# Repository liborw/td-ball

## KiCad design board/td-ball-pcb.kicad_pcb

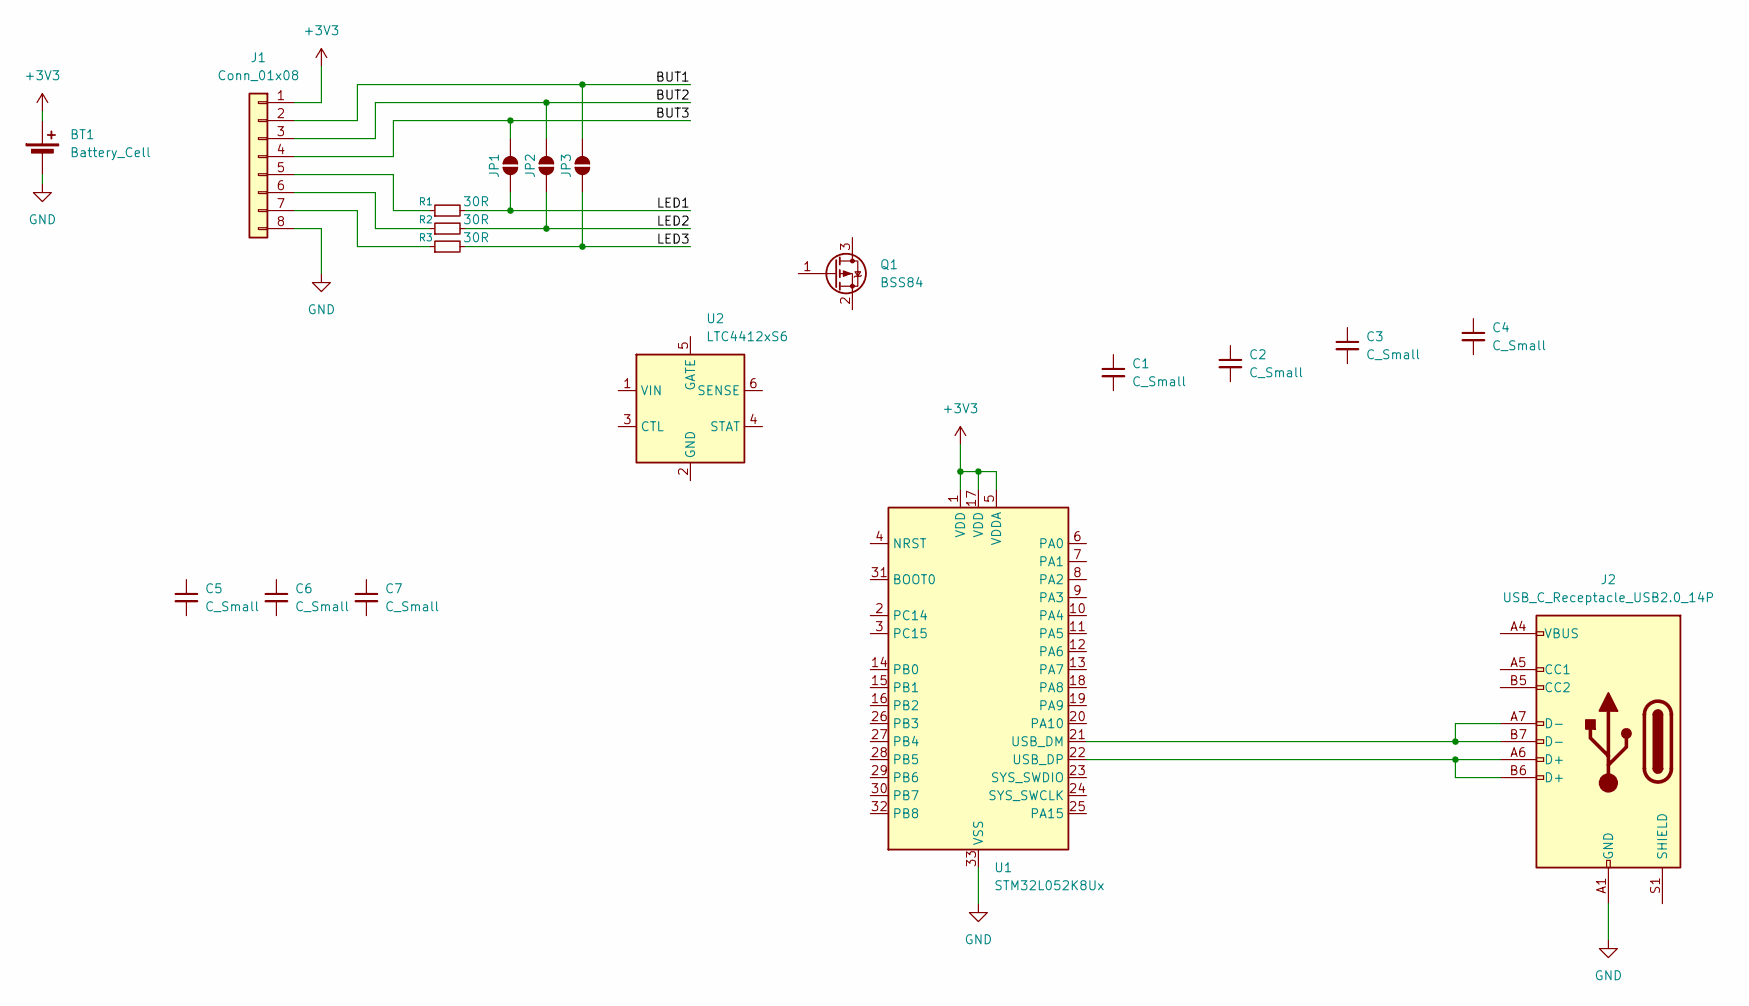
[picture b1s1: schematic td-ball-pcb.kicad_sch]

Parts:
BT1: Battery_Cell; MYOUNG_BS-24-B4AA016_CR2450
C1, C2, C3, C4: C_Small; C_0603_1608Metric
C5, C6, C7: C_Small; C_1210_3225Metric
J1: Conn_01x08; JST_SH_BM08B-SRSS-TB_1x08-1MP_P1.00mm_Vertical
J2: USB_C_Receptacle_USB2.0_14P; USB_C_Receptacle_G-Switch_GT-USB-7051x
JP1, JP2, JP3: SolderJumper_2_Open; SolderJumper-2_P1.3mm_Open_RoundedPad1.0x1.5mm
Q1: BSS84; SOT-23
R1, R2, R3: 30R; R_0603_1608Metric
U1: STM32L052K8Ux; QFN-32-1EP_5x5mm_P0.5mm_EP3.45x3.45mm
U2: LTC4412xS6; TSOT-23-6

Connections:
+3V3: BT1.1 (+), J1.1, U1.1 (VDD), U1.5 (VDDA), U1.17 (VDD)
/BUT1: J1.2, JP3.2 (B)
/BUT2: J1.3, JP2.2 (B)
/BUT3: J1.4, JP1.2 (B)
/LED1: JP1.1 (A), R1.2
/LED2: JP2.1 (A), R2.2
/LED3: JP3.1 (A), R3.2
GND: BT1.2 (-), J1.8, J2.A1 (GND), J2.A12 (GND), J2.B1 (GND), J2.B12 (GND), U1.33 (VSS)
unnamed: J1.5, R1.1
unnamed: J1.6, R2.1
unnamed: J1.7, R3.1
unnamed: J2.A4 (VBUS), J2.A9 (VBUS), J2.B4 (VBUS), J2.B9 (VBUS)
unnamed: J2.A7 (D-), J2.B7 (D-), U1.21 (USB_DM)
unnamed: J2.A6 (D+), J2.B6 (D+), U1.22 (USB_DP)

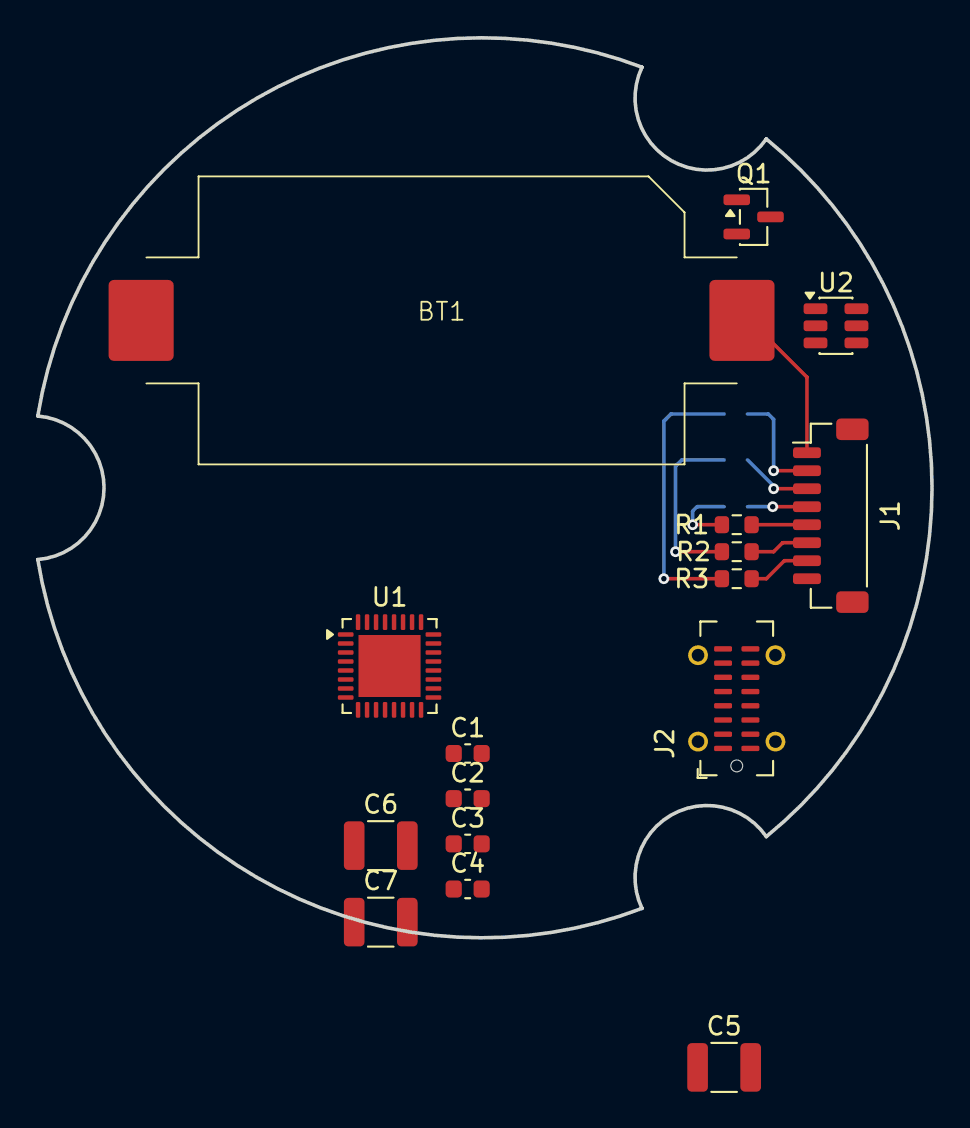
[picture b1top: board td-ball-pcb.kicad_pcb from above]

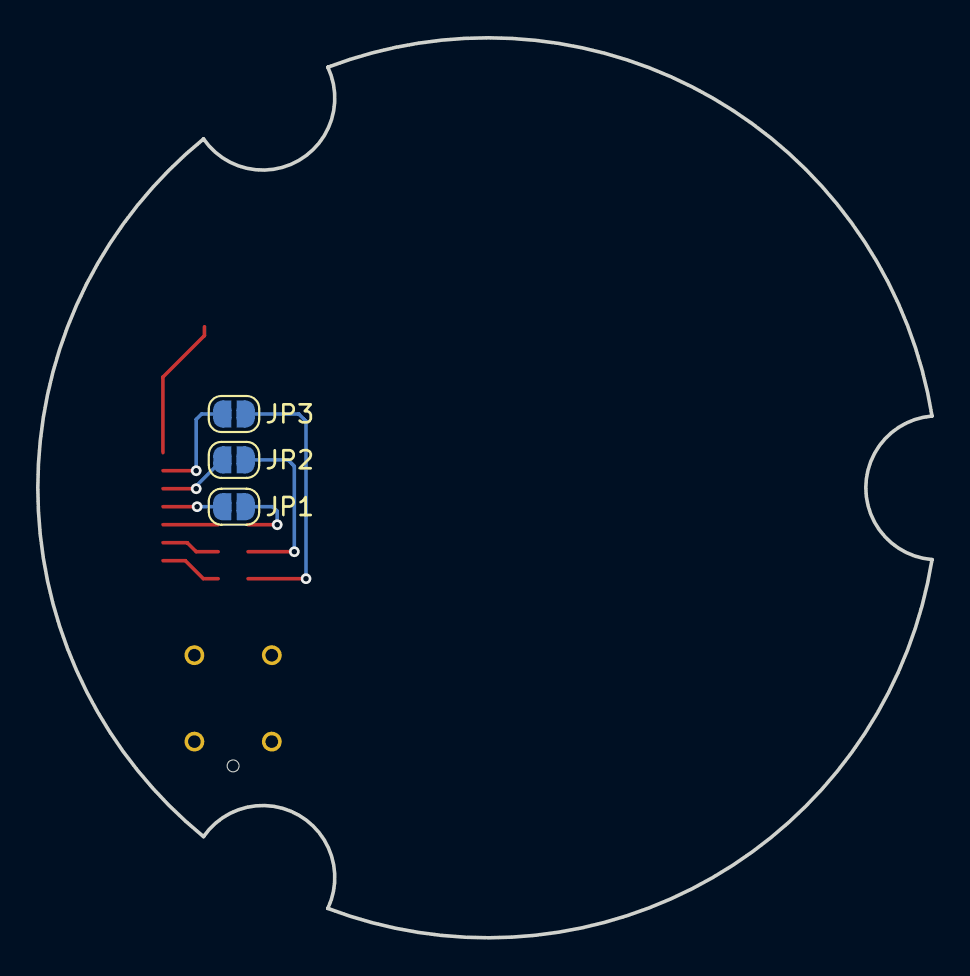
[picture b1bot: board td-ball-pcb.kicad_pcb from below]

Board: 2 copper layers, 49.7 x 50.0 mm, 19 parts (3 on the bottom side), 14 nets.

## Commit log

2025-10-30 Add ball model
